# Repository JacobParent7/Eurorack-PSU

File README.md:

# Eurorack-PSU
This repository has the KiCAD design files for a simple +12/-12V Eurorack PSU PCB. It also includes the BOM, CPL, and compressed GERBER files to order directly from a PCB Fab.

## Schematic Design

## Footprint Design

## Design Description
This design utilizes a wall wart AC/AC converter which provides a ~17Vpp AC signal to the board. The board then rectifies this signal into its positive and negative parts and filters the rectified signals to a max ripple of 1V for the inputs of both regulators. This filtered signal is sent to two voltage regulators which have high frequency tantalum compensation capacitors. These regulators directly provide the -12/+12V rails. The LM7812 does not have a built in protection diode so that is why it's included.

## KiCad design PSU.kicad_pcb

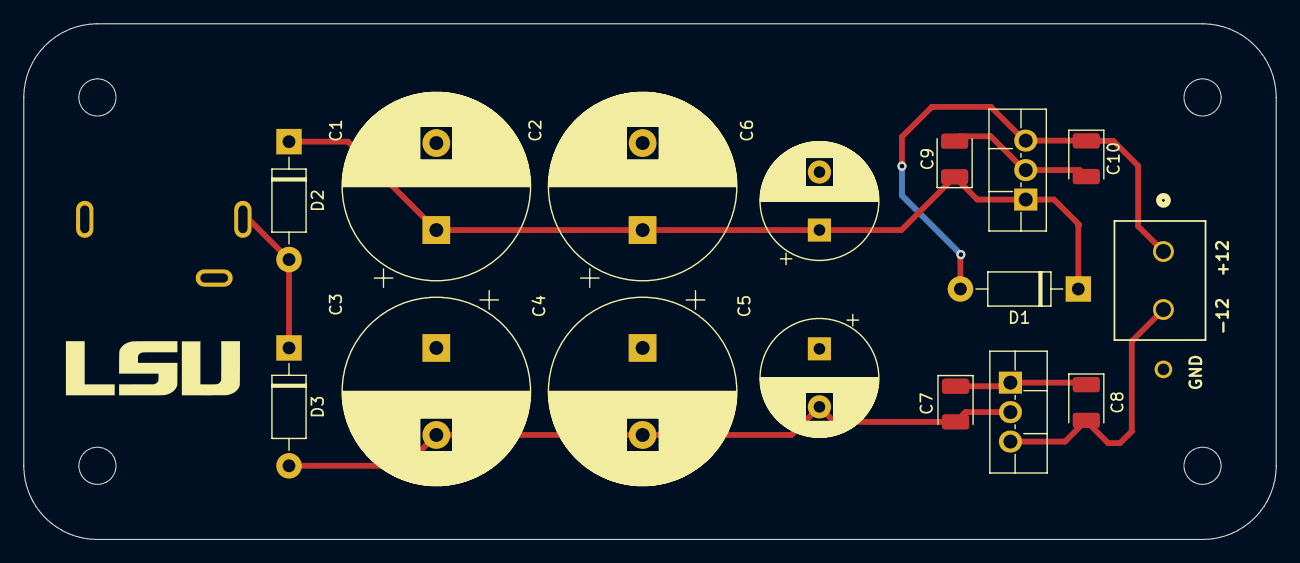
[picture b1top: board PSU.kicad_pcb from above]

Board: 2 copper layers, 107.9 x 44.5 mm, 21 parts (0 on the bottom side), 6 nets.

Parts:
C1, C2, C3: 4700uf; CP_Radial_D16.0mm_P7.50mm
C4: 4700uF; CP_Radial_D16.0mm_P7.50mm
C5, C6: 2000uF; CP_Radial_D10.0mm_P5.00mm
C7, C8, C9, C10: 1uF; CP_EIA-3528-21_Kemet-B
D1, D2, D3: 1N4007; D_DO-41_SOD81_P10.16mm_Horizontal
H1, H2, H3, H4: MountingHole; MountingHole_3.2mm_M3
J1: MJ-3536NG; MJ-3536NG_CUD
J2: 691137710002; CONN2_710002_WRE
LM7812: L7812; TO-220F-3_Vertical
U2: L7912; TO-220F-3_Vertical

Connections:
+12V: C10.1, D1.2 (A), J2.1, LM7812.3 (OUT)
-12V: C8.2, J2.2, U2.3 (VO)
GND: C1.2, C2.2, C3.1, C4.1, C5.1, C6.2, C7.1, C8.1, C9.2, C10.2, J1.6, J2.3, LM7812.2 (GND), U2.1 (GND)
unnamed: C1.1, C2.1, C6.1, C9.1, D1.1 (K), D2.1 (K), LM7812.1 (IN)
unnamed: D2.2 (A), D3.1 (K), J1.6
unnamed: C3.2, C4.2, C5.2, C7.2, D3.2 (A), U2.2 (VI)

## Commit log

2023-10-28 PCB Design and FAB files
2023-11-13 Update README.md
    Boards came in
